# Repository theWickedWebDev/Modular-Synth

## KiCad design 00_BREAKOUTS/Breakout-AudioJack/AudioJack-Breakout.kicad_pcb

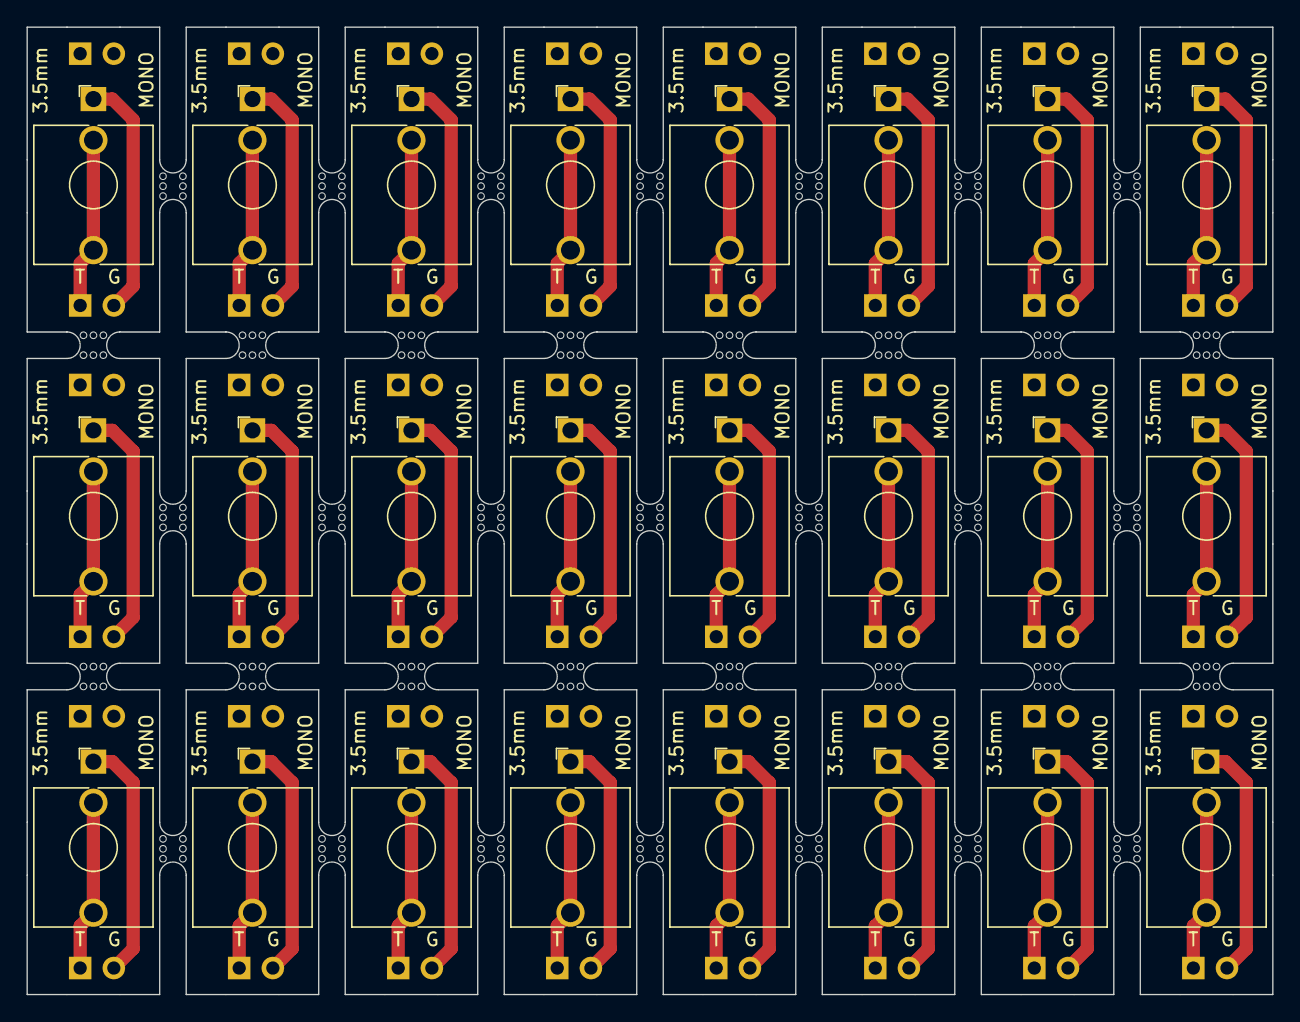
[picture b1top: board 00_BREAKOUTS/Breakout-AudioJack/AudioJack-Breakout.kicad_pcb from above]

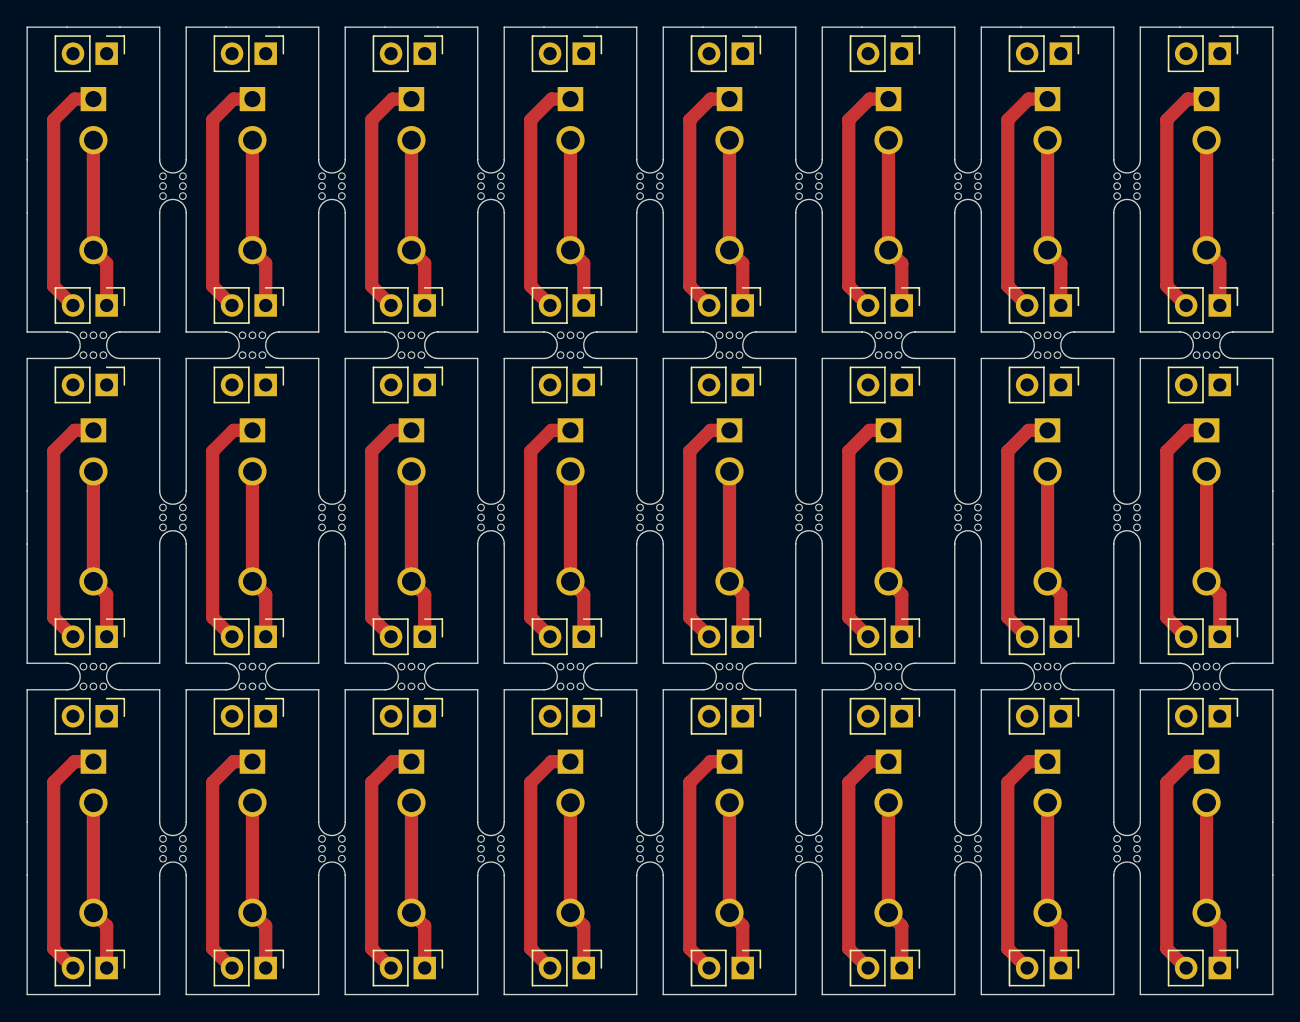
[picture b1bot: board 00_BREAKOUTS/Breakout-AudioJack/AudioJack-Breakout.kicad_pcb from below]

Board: 2 copper layers, 94.0 x 73.0 mm, 109 parts (48 on the bottom side), 2 nets.

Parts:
J3, J5, J7, J12, J15, J18, J21, J24, J27, J30, J33, J36, J39, J42, J45, J48, J51, J54, J57, J60, J63, J66, J69, J72: AudioJack2_Ground; 3.5mm-mono-jack-eurorack-2
J4, J6, J8, J9, J10, J11, J13, J14, J16, J17, J19, J20, J22, J23, J25, J26, J28, J29, J31, J32, J34, J35, J37, J38, J40, J41, J43, J44, J46, J47, J49, J50, J52, J53, J55, J56, J58, J59, J61, J62, J64, J65, J67, J68, J70, J71, J73, J74: Conn_01x02; PinHeader_1x02_P2.54mm_Vertical
mouse-bite-2mm-slot1, mouse-bite-2mm-slot1#2, mouse-bite-2mm-slot2, mouse-bite-2mm-slot3, mouse-bite-2mm-slot4, mouse-bite-2mm-slot5, mouse-bite-2mm-slot6, mouse-bite-2mm-slot7, mouse-bite-2mm-slot8, mouse-bite-2mm-slot9, mouse-bite-2mm-slot10, mouse-bite-2mm-slot11, mouse-bite-2mm-slot12, mouse-bite-2mm-slot13, mouse-bite-2mm-slot14, mouse-bite-2mm-slot16, mouse-bite-2mm-slot17, mouse-bite-2mm-slot18, mouse-bite-2mm-slot19, mouse-bite-2mm-slot20, mouse-bite-2mm-slot21, mouse-bite-2mm-slot22, mouse-bite-2mm-slot23, mouse-bite-2mm-slot24, mouse-bite-2mm-slot25, mouse-bite-2mm-slot26, mouse-bite-2mm-slot27, mouse-bite-2mm-slot28, mouse-bite-2mm-slot29, mouse-bite-2mm-slot30, mouse-bite-2mm-slot33, mouse-bite-2mm-slot35, mouse-bite-2mm-slot37, mouse-bite-2mm-slot39, mouse-bite-2mm-slot41, mouse-bite-2mm-slot43, mouse-bite-2mm-slot45: VAL**; mouse-bite-2mm-slot

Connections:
unnamed: J3.G, J4.2, J5.G, J6.2, J7.G, J10.2, J12.G, J13.2, J15.G, J16.2, J18.G, J19.2, J21.G, J22.2, J24.G, J25.2, J27.G, J28.2, J30.G, J31.2, J33.G, J34.2, J36.G, J37.2, J39.G, J40.2, J42.G, J43.2, J45.G, J46.2, J48.G, J49.2, J51.G, J52.2, J54.G, J55.2, J57.G, J58.2, J60.G, J61.2, J63.G, J64.2, J66.G, J67.2, J69.G, J70.2, J72.G, J73.2
unnamed: J3.S, J3.T, J4.1, J5.S, J5.T, J6.1, J7.S, J7.T, J10.1, J12.S, J12.T, J13.1, J15.S, J15.T, J16.1, J18.S, J18.T, J19.1, J21.S, J21.T, J22.1, J24.S, J24.T, J25.1, J27.S, J27.T, J28.1, J30.S, J30.T, J31.1, J33.S, J33.T, J34.1, J36.S, J36.T, J37.1, J39.S, J39.T, J40.1, J42.S, J42.T, J43.1, J45.S, J45.T, J46.1, J48.S, J48.T, J49.1, J51.S, J51.T, J52.1, J54.S, J54.T, J55.1, J57.S, J57.T, J58.1, J60.S, J60.T, J61.1, J63.S, J63.T, J64.1, J66.S, J66.T, J67.1, J69.S, J69.T, J70.1, J72.S, J72.T, J73.1

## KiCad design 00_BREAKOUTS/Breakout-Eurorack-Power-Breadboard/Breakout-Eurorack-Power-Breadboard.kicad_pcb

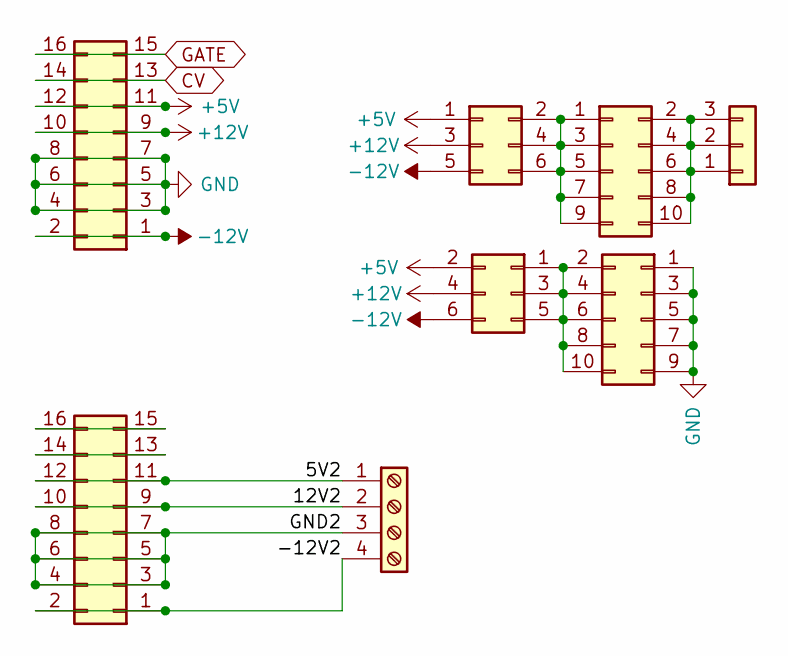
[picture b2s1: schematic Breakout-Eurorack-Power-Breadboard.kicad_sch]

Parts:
J1, J7: Conn_02x20_Odd_Even; IDC-Header_2x08_P2.54mm_Vertical
J2, J3: Conn_02x02_Odd_Even; PinHeader_2x05_P2.54mm_Vertical
J4, J5: Conn_02x03_Odd_Even; PinHeader_2x03_P2.54mm_Vertical
J6: Conn_01x03; PinHeader_1x03_P2.54mm_Vertical
J8: Screw_Terminal_01x04; TerminalBlock_Phoenix_MKDS-1,5-4_1x04_P5.00mm_Horizontal

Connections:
+5V: J1.11, J1.12, J4.2, J5.1
+12V: J1.9, J1.10, J4.4, J5.3
-12V: J1.1, J1.2, J4.6, J5.5
/5V2: J7.11, J7.12, J8.1
/12V2: J7.9, J7.10, J8.2
/-12V2: J7.1, J7.2, J8.4
/GND2: J7.3, J7.4, J7.5, J7.6, J7.7, J7.8, J8.3
CV: J1.13, J1.14
GATE: J1.15, J1.16
GND: J1.3, J1.4, J1.5, J1.6, J1.7, J1.8, J3.1, J3.3, J3.5, J3.7, J3.9
unnamed: J2.1, J2.3, J2.5, J2.7, J2.9, J5.2, J5.4, J5.6
unnamed: J2.2, J2.4, J2.6, J2.8, J2.10, J6.1, J6.2, J6.3
unnamed: J3.2, J3.4, J3.6, J3.8, J3.10, J4.1, J4.3, J4.5
unnamed: J7.13, J7.14
unnamed: J7.15, J7.16

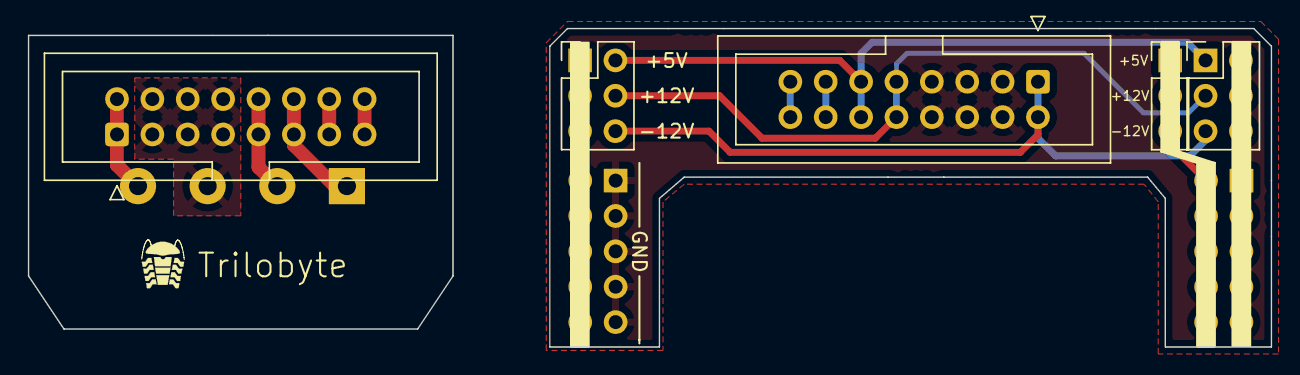
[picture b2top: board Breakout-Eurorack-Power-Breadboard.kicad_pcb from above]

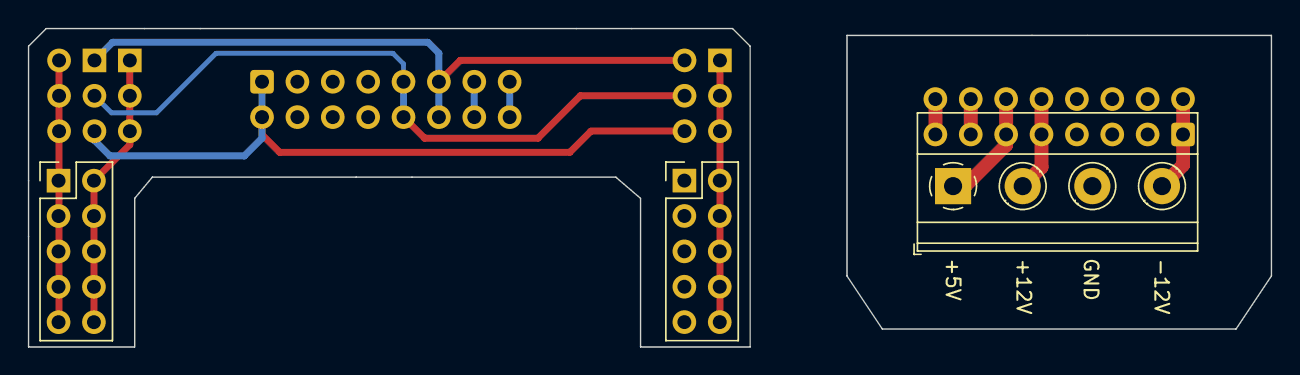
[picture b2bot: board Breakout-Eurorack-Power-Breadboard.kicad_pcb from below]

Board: 2 copper layers, 89.2 x 22.9 mm, 8 parts (3 on the bottom side), 15 nets.

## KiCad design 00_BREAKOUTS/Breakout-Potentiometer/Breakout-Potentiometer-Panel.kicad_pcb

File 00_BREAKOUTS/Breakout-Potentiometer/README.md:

# Potentiometer - Breakout Boards

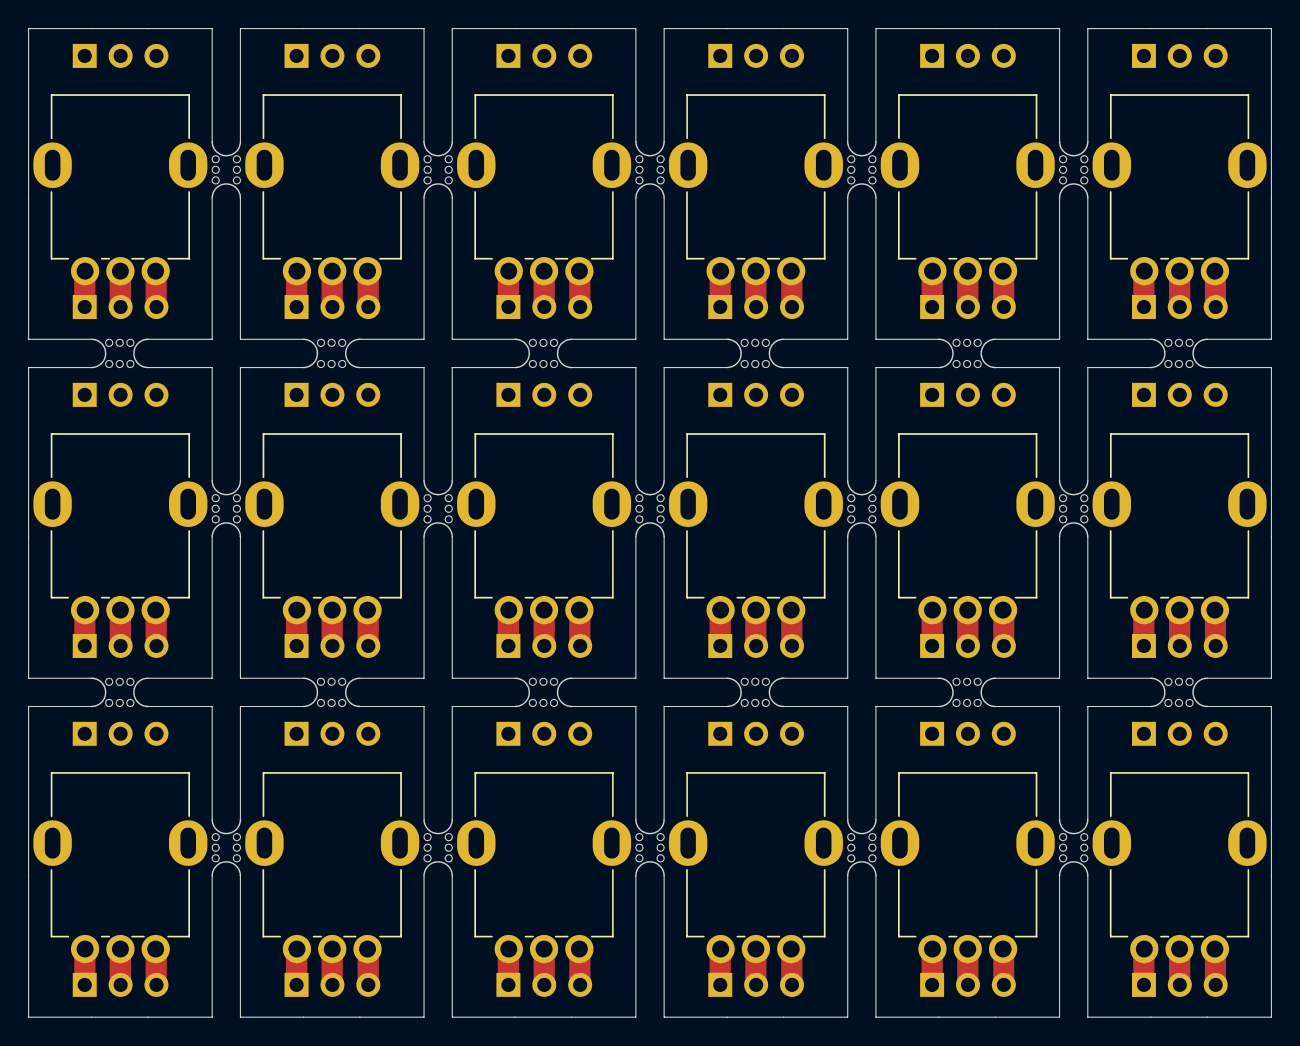
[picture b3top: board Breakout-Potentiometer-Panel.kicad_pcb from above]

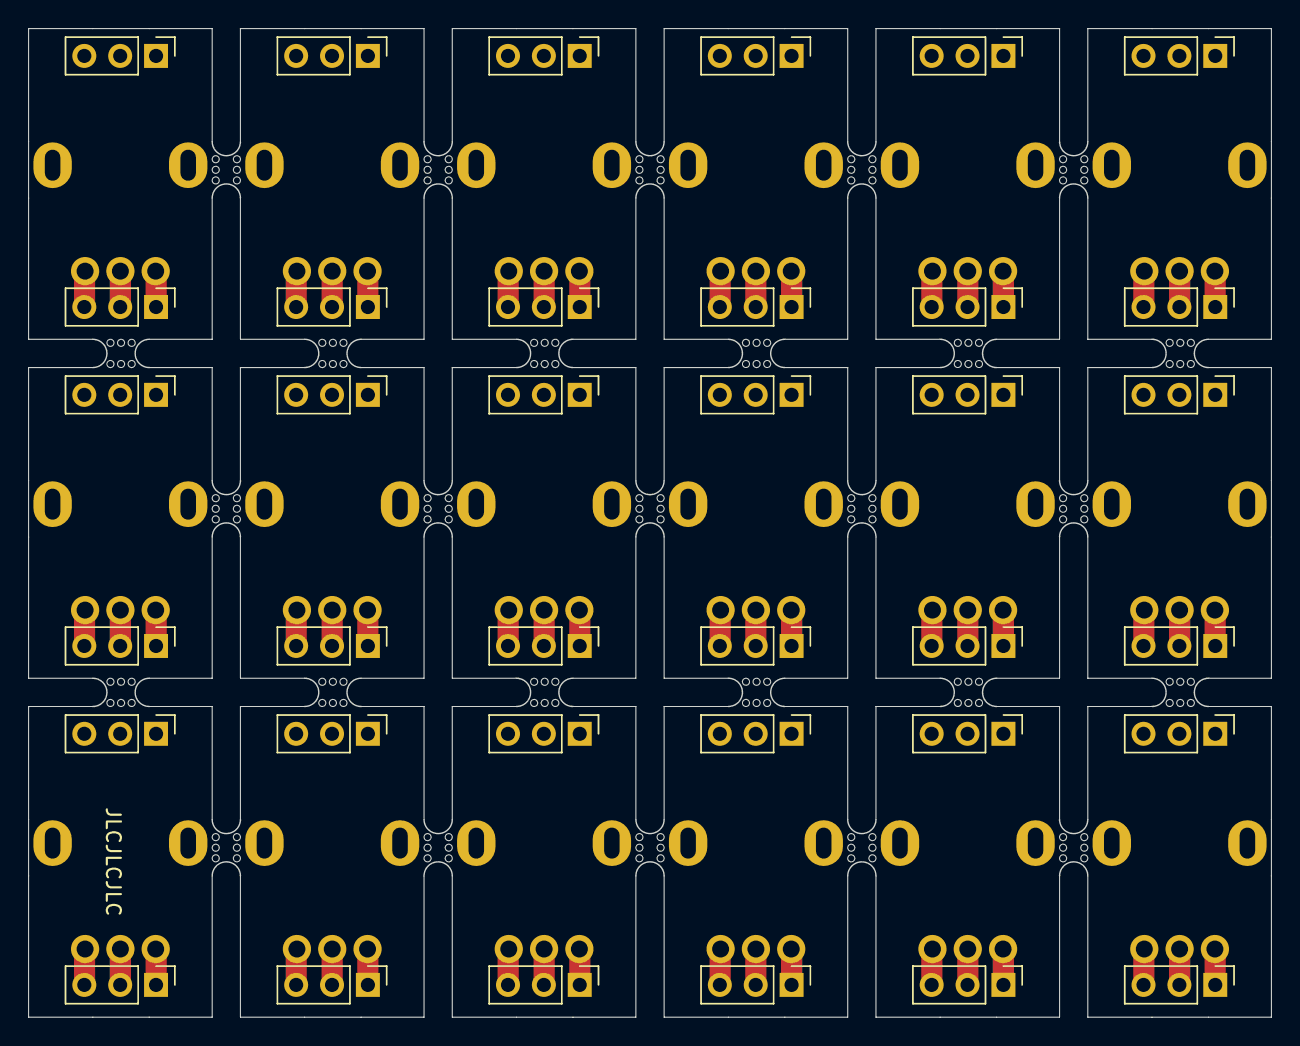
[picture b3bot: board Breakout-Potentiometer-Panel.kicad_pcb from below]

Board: 2 copper layers, 88.0 x 70.0 mm, 81 parts (36 on the bottom side), 3 nets.

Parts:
J1, J2, J3, J4, J5, J6, J7, J8, J9, J10, J11, J12, J13, J14, J15, J16, J17, J18, J19, J20, J21, J22, J23, J24, J25, J26, J27, J28, J29, J30, J31, J32, J33, J34, J35, J36: Conn_01x03; PinHeader_1x03_P2.54mm_Vertical
RV1, RV2, RV3, RV4, RV5, RV6, RV7, RV8, RV9, RV10, RV11, RV12, RV13, RV14, RV15, RV16, RV17, RV18: R_Potentiometer_US; alpha-9mm-potentiometer
mouse-bite-2mm-slot1, mouse-bite-2mm-slot3, mouse-bite-2mm-slot5, mouse-bite-2mm-slot7, mouse-bite-2mm-slot9, mouse-bite-2mm-slot12, mouse-bite-2mm-slot13, mouse-bite-2mm-slot14, mouse-bite-2mm-slot15, mouse-bite-2mm-slot16, mouse-bite-2mm-slot17, mouse-bite-2mm-slot18, mouse-bite-2mm-slot19, mouse-bite-2mm-slot20, mouse-bite-2mm-slot21, mouse-bite-2mm-slot22, mouse-bite-2mm-slot24, mouse-bite-2mm-slot25, mouse-bite-2mm-slot26, mouse-bite-2mm-slot27, mouse-bite-2mm-slot28, mouse-bite-2mm-slot29, mouse-bite-2mm-slot30, mouse-bite-2mm-slot31, mouse-bite-2mm-slot32, mouse-bite-2mm-slot33, mouse-bite-2mm-slot34: VAL**; mouse-bite-2mm-slot

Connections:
unnamed: J2.1, J4.1, J6.1, J8.1, J10.1, J12.1, J14.1, J16.1, J18.1, J20.1, J22.1, J24.1, J26.1, J28.1, J30.1, J32.1, J34.1, J36.1, RV1.1, RV2.1, RV3.1, RV4.1, RV5.1, RV6.1, RV7.1, RV8.1, RV9.1, RV10.1, RV11.1, RV12.1, RV13.1, RV14.1, RV15.1, RV16.1, RV17.1, RV18.1
unnamed: J2.2, J4.2, J6.2, J8.2, J10.2, J12.2, J14.2, J16.2, J18.2, J20.2, J22.2, J24.2, J26.2, J28.2, J30.2, J32.2, J34.2, J36.2, RV1.2, RV2.2, RV3.2, RV4.2, RV5.2, RV6.2, RV7.2, RV8.2, RV9.2, RV10.2, RV11.2, RV12.2, RV13.2, RV14.2, RV15.2, RV16.2, RV17.2, RV18.2
unnamed: J2.3, J4.3, J6.3, J8.3, J10.3, J12.3, J14.3, J16.3, J18.3, J20.3, J22.3, J24.3, J26.3, J28.3, J30.3, J32.3, J34.3, J36.3, RV1.3, RV2.3, RV3.3, RV4.3, RV5.3, RV6.3, RV7.3, RV8.3, RV9.3, RV10.3, RV11.3, RV12.3, RV13.3, RV14.3, RV15.3, RV16.3, RV17.3, RV18.3

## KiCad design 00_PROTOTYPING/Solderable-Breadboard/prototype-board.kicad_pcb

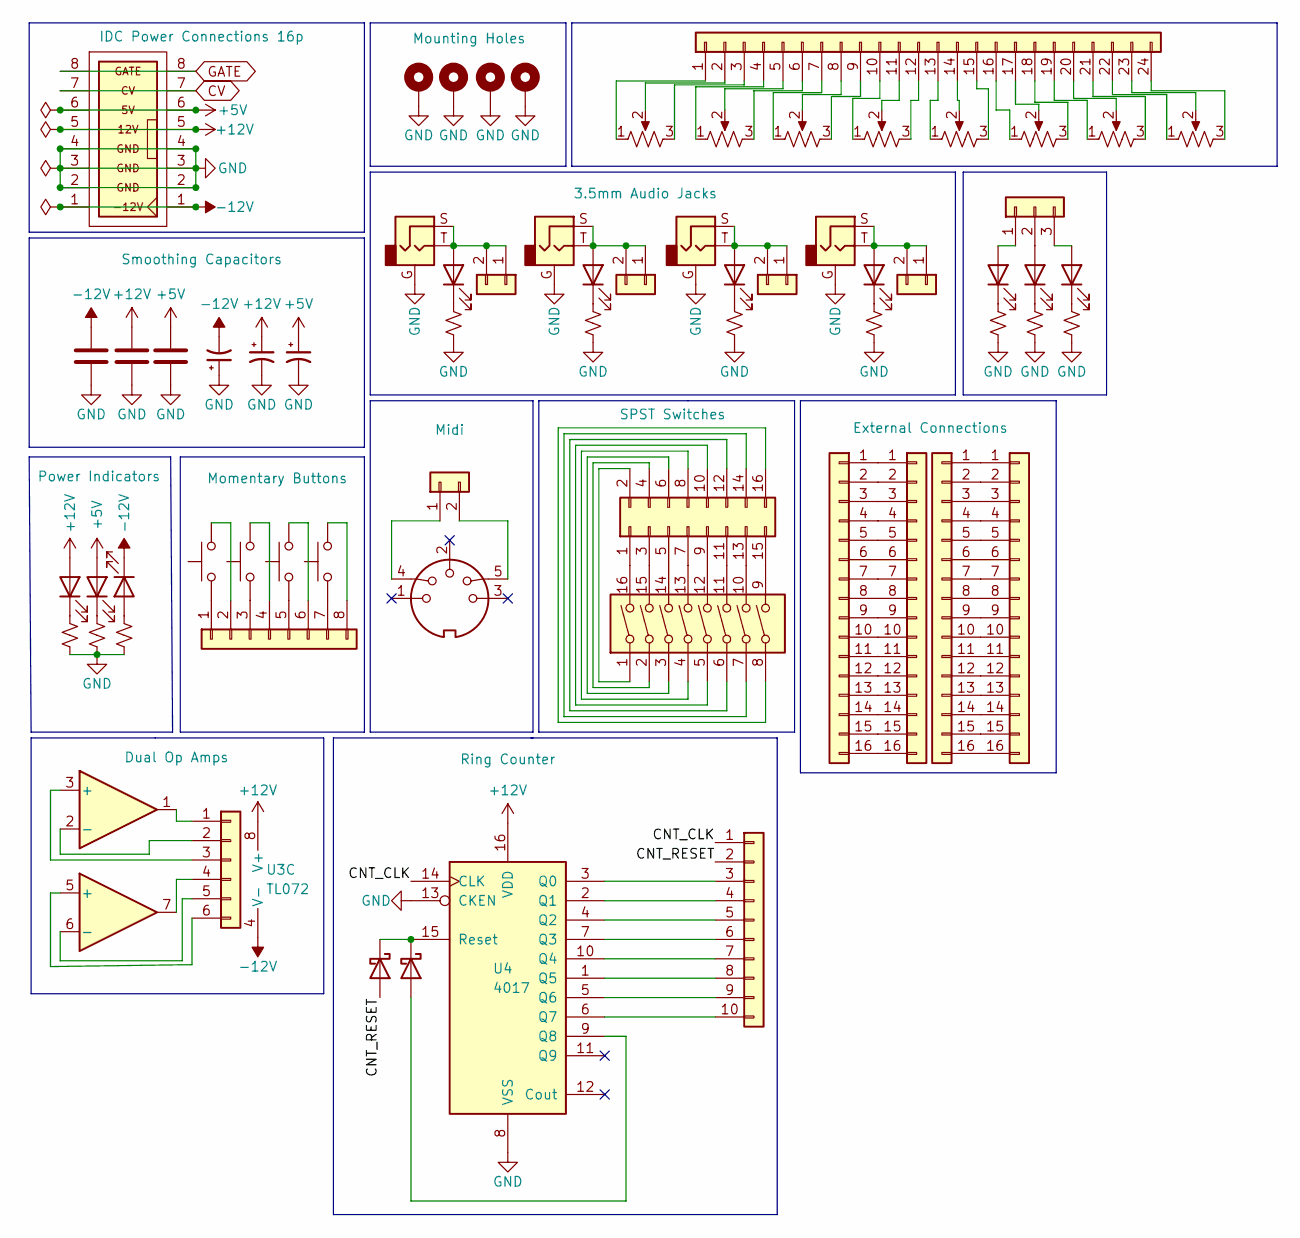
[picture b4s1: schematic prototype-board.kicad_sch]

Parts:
C1, C2, C3: C; C_0805_2012Metric
C4, C5, C6: C_Polarized_Small_US; CP_Elec_6.3x7.7
D1, D2, D3, D4, D5, D6, D7, D8, D11, D12: LED; LED_0805_2012Metric-Blue
D9, D10: BAT43W-V; D_SOD-123
H1, H2, H3, H4: MountingHole_Pad; MountingHole_3mm_Pad_Via
J1, J4, J6, J8, J20: Conn_01x02; PinHeader_1x02_P2.54mm_Vertical
J2, J3, J5, J7: AudioJack2_Ground; 3.5mm-mono-jack-eurorack-2
J9: Conn_01x24; PinSocket_1x24_P2.54mm_Vertical
J10: Conn_01x03; PinHeader_1x03_P2.54mm_Vertical
J11: Conn_02x08_Odd_Even; PinHeader_2x08_P2.54mm_Vertical
J12: Conn_01x06; PinHeader_1x06_P2.54mm_Vertical
J13: Conn_01x10; PinHeader_1x10_P2.54mm_Vertical
J15, J17: Conn_01x16; PinHeader_1x16_P2.54mm_Vertical
J16, J18: Conn_01x16; PinHeader_1x16_P2.54mm_Horizontal
J19: DIN-5_180degree; MIDI_DIN5
J21: Conn_01x08; PinHeader_1x08_P2.54mm_Vertical
R1, R2, R3, R4, R5, R6, R7, R8, R9, R10: R_Small_US; R_0805_2012Metric
RV1, RV2, RV3, RV4, RV5, RV6, RV7, RV8: R_Potentiometer_US; alpha-9mm-potentiometer
SW1: SW_DIP_x08; SW_DIP_SPSTx08_Slide_9.78x22.5mm_W7.62mm_P2.54mm
SW2, SW3, SW4, SW5: SW_Push; SW_PUSH_6mm
U1: Eurorack_IDE_16P; IDC-Socket-Eurorack_16p_2.54mm
U3: TL072; DIP-8_W7.62mm
U4: 4017; SOIC-16_3.9x9.9mm_P1.27mm

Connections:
+5V: C3.1, C6.1, D7.2 (A), U1.6 (5V)
+12V: C2.1, C4.1, D6.2 (A), U1.5 (12V), U3.8 (V+), U4.16 (VDD)
-12V: C1.1, C5.2, D8.1 (K), U1.1 (-12V), U3.4 (V-)
/CNT_CLK: J13.1, U4.14 (CLK)
/CNT_RESET: D9.2 (A), J13.2
CV: U1.7 (CV)
GATE: U1.8 (GATE)
GND: C1.2, C2.2, C3.2, C4.2, C5.1, C6.2, H1.1, H2.1, H3.1, H4.1, J2.G, J3.G, J5.G, J7.G, R1.2, R2.2, R3.2, R4.2, R5.2, R6.2, R7.2, R8.2, R9.2, R10.2, U1.2 (GND), U1.3 (GND), U1.4 (GND), U4.8 (VSS), U4.13 (CKEN)
unnamed: D1.1 (K), R1.1
unnamed: D1.2 (A), J1.1, J1.2, J3.S, J3.T
unnamed: D2.1 (K), R2.1
unnamed: D2.2 (A), J2.S, J2.T, J4.1, J4.2
unnamed: D3.1 (K), R3.1
unnamed: D3.2 (A), J5.S, J5.T, J6.1, J6.2
unnamed: D4.1 (K), R4.1
unnamed: D4.2 (A), J7.S, J7.T, J8.1, J8.2
unnamed: D5.1 (K), R5.1
unnamed: D5.2 (A), J10.1
unnamed: D6.1 (K), R8.1
unnamed: D7.1 (K), R9.1
unnamed: D8.2 (A), R10.1
unnamed: D9.1 (K), D10.1 (K), U4.15 (Reset)
unnamed: D10.2 (A), U4.9 (Q8)
unnamed: D11.1 (K), R6.1
unnamed: D11.2 (A), J10.2
unnamed: D12.1 (K), R7.1
unnamed: D12.2 (A), J10.3
unnamed: J9.1, RV1.1
unnamed: J9.2, RV1.2
unnamed: J9.3, RV1.3
unnamed: J9.4, RV2.1
unnamed: J9.5, RV2.2
unnamed: J9.6, RV2.3
unnamed: J9.7, RV3.1
unnamed: J9.8, RV3.2
unnamed: J9.9, RV3.3
unnamed: J9.10, RV4.1
unnamed: J9.11, RV4.2
unnamed: J9.12, RV4.3
unnamed: J9.13, RV5.1
unnamed: J9.14, RV5.2
unnamed: J9.15, RV5.3
unnamed: J9.16, RV6.1
unnamed: J9.17, RV6.2
unnamed: J9.18, RV6.3
unnamed: J9.19, RV7.1
unnamed: J9.20, RV7.2
unnamed: J9.21, RV7.3
unnamed: J9.22, RV8.1
unnamed: J9.23, RV8.2
unnamed: J9.24, RV8.3
unnamed: J11.1, SW1.16
unnamed: J11.2, SW1.1
unnamed: J11.3, SW1.15
unnamed: J11.4, SW1.2
unnamed: J11.5, SW1.14
unnamed: J11.6, SW1.3
unnamed: J11.7, SW1.13
unnamed: J11.8, SW1.4
unnamed: J11.9, SW1.12
unnamed: J11.10, SW1.5
unnamed: J11.11, SW1.11
unnamed: J11.12, SW1.6
unnamed: J11.13, SW1.10
unnamed: J11.14, SW1.7
unnamed: J11.15, SW1.9
unnamed: J11.16, SW1.8
unnamed: J12.1, U3.1
unnamed: J12.2, U3.2 (-)
unnamed: J12.3, U3.3 (+)
unnamed: J12.4, U3.7
unnamed: J12.5, U3.6 (-)
unnamed: J12.6, U3.5 (+)
unnamed: J13.3, U4.3 (Q0)
unnamed: J13.4, U4.2 (Q1)
unnamed: J13.5, U4.4 (Q2)
unnamed: J13.6, U4.7 (Q3)
unnamed: J13.7, U4.10 (Q4)
unnamed: J13.8, U4.1 (Q5)
unnamed: J13.9, U4.5 (Q6)
unnamed: J13.10, U4.6 (Q7)
unnamed: J15.1, J16.1
unnamed: J15.2, J16.2
unnamed: J15.3, J16.3
unnamed: J15.4, J16.4
unnamed: J15.5, J16.5
unnamed: J15.6, J16.6
unnamed: J15.7, J16.7
unnamed: J15.8, J16.8
unnamed: J15.9, J16.9
unnamed: J15.10, J16.10
unnamed: J15.11, J16.11
unnamed: J15.12, J16.12
unnamed: J15.13, J16.13
unnamed: J15.14, J16.14
unnamed: J15.15, J16.15
unnamed: J15.16, J16.16
unnamed: J17.1, J18.1
unnamed: J17.2, J18.2
unnamed: J17.3, J18.3
unnamed: J17.4, J18.4
unnamed: J17.5, J18.5
unnamed: J17.6, J18.6
unnamed: J17.7, J18.7
unnamed: J17.8, J18.8
unnamed: J17.9, J18.9
unnamed: J17.10, J18.10
unnamed: J17.11, J18.11
unnamed: J17.12, J18.12
unnamed: J17.13, J18.13
unnamed: J17.14, J18.14
unnamed: J17.15, J18.15
unnamed: J17.16, J18.16
unnamed: J19.4, J20.1
unnamed: J19.5, J20.2
unnamed: J21.1, SW2.1
unnamed: J21.2, SW2.2
unnamed: J21.3, SW3.1
unnamed: J21.4, SW3.2
unnamed: J21.5, SW4.1
unnamed: J21.6, SW4.2
unnamed: J21.7, SW5.1
unnamed: J21.8, SW5.2

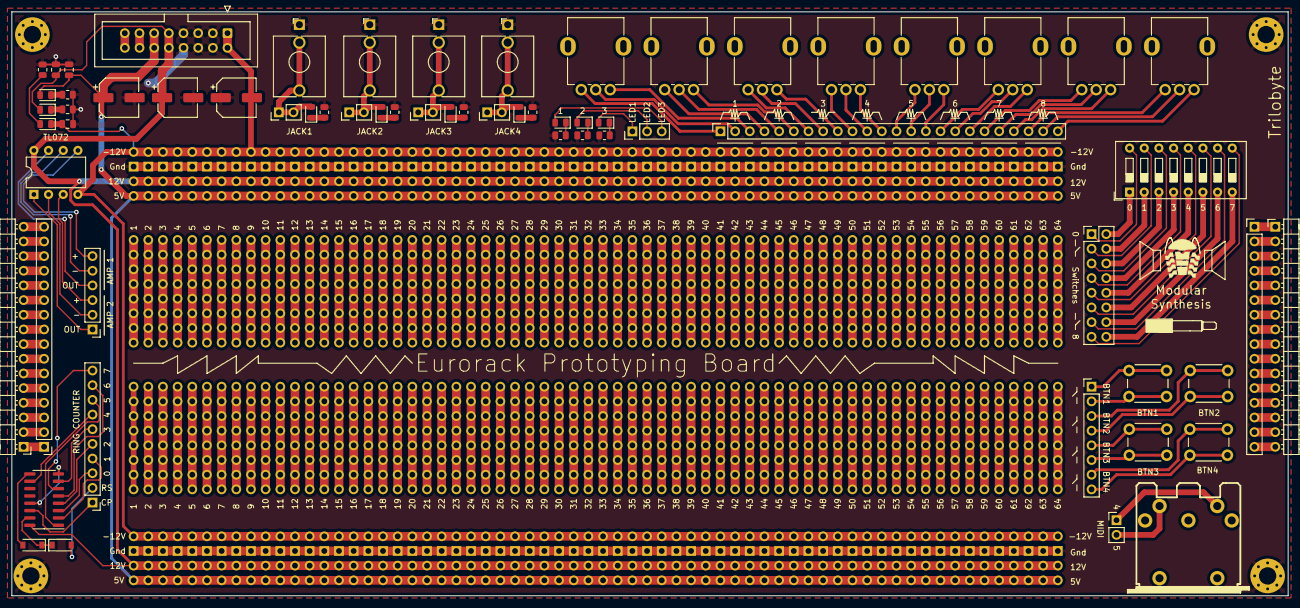
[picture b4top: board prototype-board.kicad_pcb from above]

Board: 2 copper layers, 221.0 x 101.1 mm, 68 parts (0 on the bottom side), 121 nets.

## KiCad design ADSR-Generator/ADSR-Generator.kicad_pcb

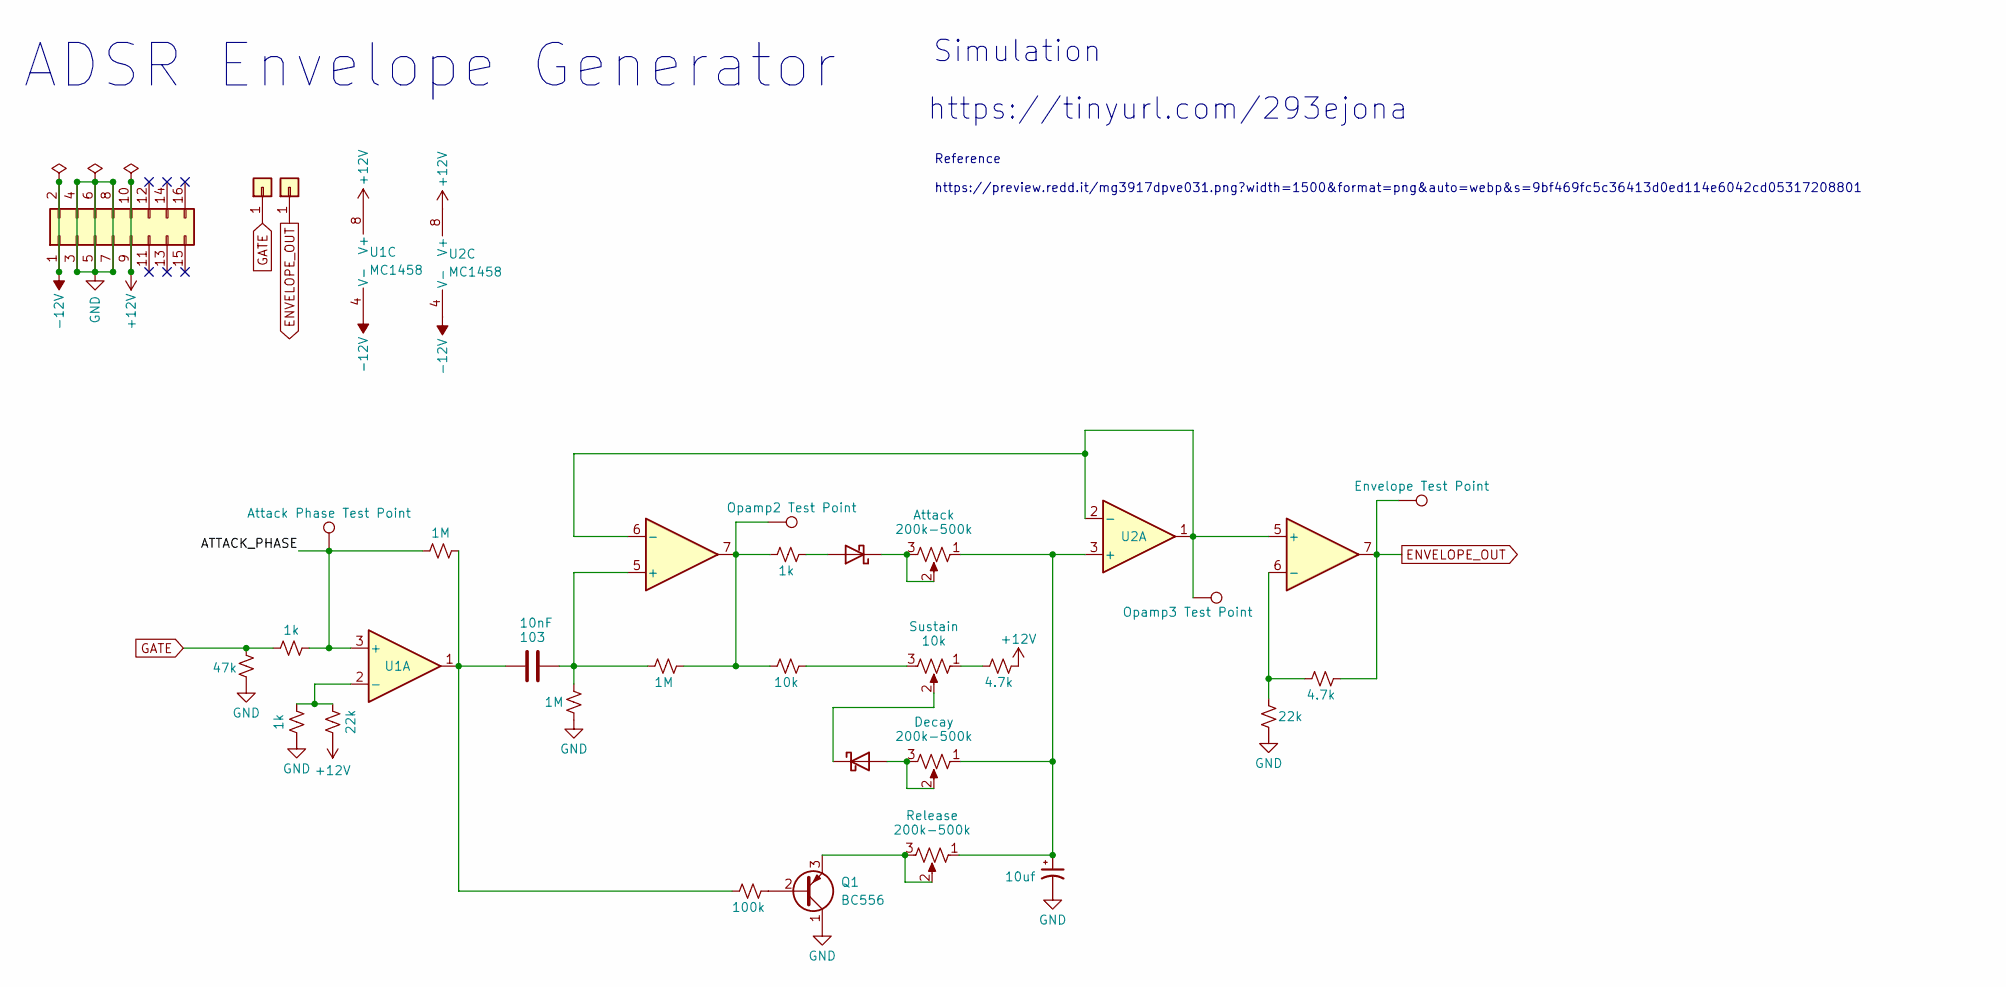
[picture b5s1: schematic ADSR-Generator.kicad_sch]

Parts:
C1: C; C_0805_2012Metric
C2: C_Polarized_Small_US; CP_Elec_5x5.4
D2, D3: BAT43W-V; D_SOD-123
J1: Conn_02x20_Odd_Even; IDC-Header_2x08_P2.54mm_Vertical
J2, J3: Conn_01x01; ACJS-MV35-3S-audio-jack
Q1: BC556; SOT23-BEC_PNP
R1, R2, R3, R4, R5, R6, R7, R8, R9, R10, R11, R12, R13: R_Small_US; R_0805_2012Metric
RV1, RV2, RV3, RV4: R_Potentiometer_US; Potentiometer_Omeg_PC16BU_Vertical
TP1, TP2, TP3, TP4: TestPoint; TestPoint_Keystone_5019_Minature
U1, U2: MC1458; SOIC-8_3.9x4.9mm_P1.27mm

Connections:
+12V: J1.9, J1.10, R4.2, R11.1, U1.8 (V+), U2.8 (V+)
-12V: J1.1, J1.2, U1.4 (V-), U2.4 (V-)
/ATTACK_PHASE: R2.2, R5.1, TP1.1, U1.3 (+)
ENVELOPE_OUT: J3.1, R13.1, TP4.1, U2.7
GATE: J2.1, R1.1, R2.1
GND: C2.2, J1.3, J1.4, J1.5, J1.6, J1.7, J1.8, Q1.1 (C), R1.2, R3.1, R6.1, R12.2
unnamed: C1.1, R5.2, R8.2, U1.1
unnamed: C1.2, R6.2, R7.2, U1.5 (+)
unnamed: C2.1, RV1.1, RV2.1, RV4.1, U2.3 (+)
unnamed: Q1.2 (B), R8.1
unnamed: Q1.3 (E), RV1.2, RV1.3
unnamed: R3.2, R4.1, U1.2 (-)
unnamed: D2.2 (A), R9.1
unnamed: R10.1, RV3.3
unnamed: R7.1, R9.2, R10.2, TP2.1, U1.7
unnamed: R11.2, RV3.1
unnamed: R12.1, R13.2, U2.6 (-)
unnamed: D2.1 (K), RV2.2, RV2.3
unnamed: D3.1 (K), RV3.2
unnamed: D3.2 (A), RV4.2, RV4.3
unnamed: TP3.1, U1.6 (-), U2.1, U2.2 (-), U2.5 (+)

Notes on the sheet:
ADSR Envelope Generator
https://tinyurl.com/293ejona
Reference https://preview.redd.it/mg3917dpve031.png?width=1500&format=png&auto=webp&s=9bf469fc5c36413d0ed114e6042cd05317208801
Simulation

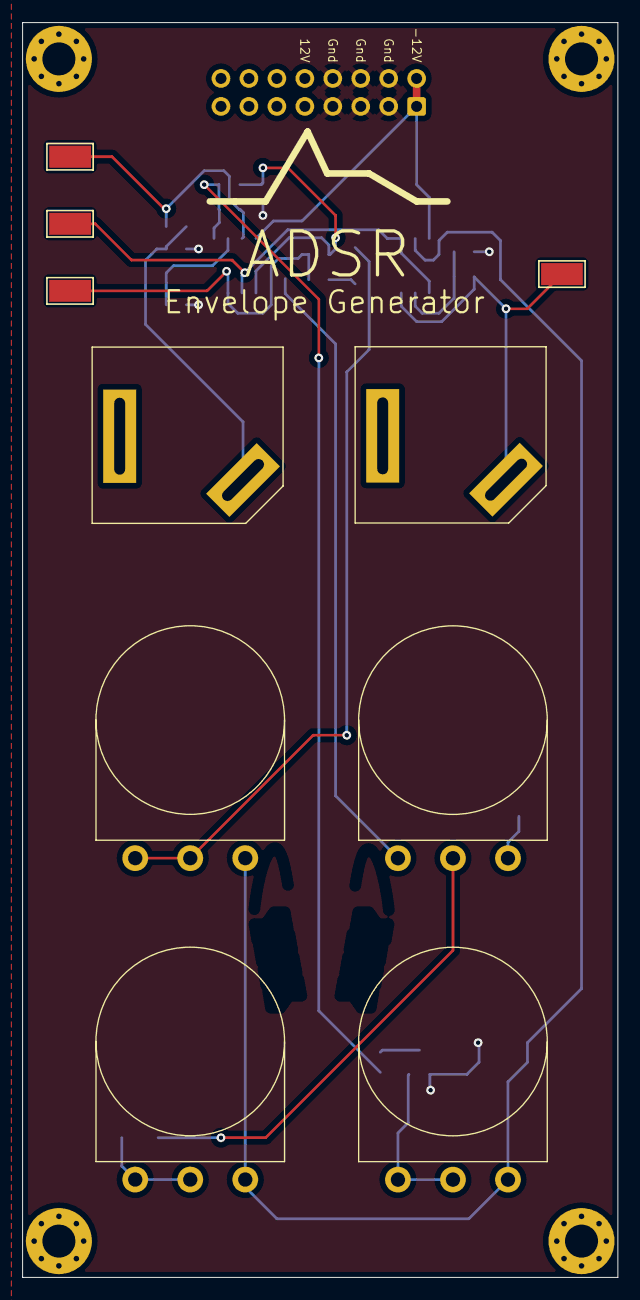
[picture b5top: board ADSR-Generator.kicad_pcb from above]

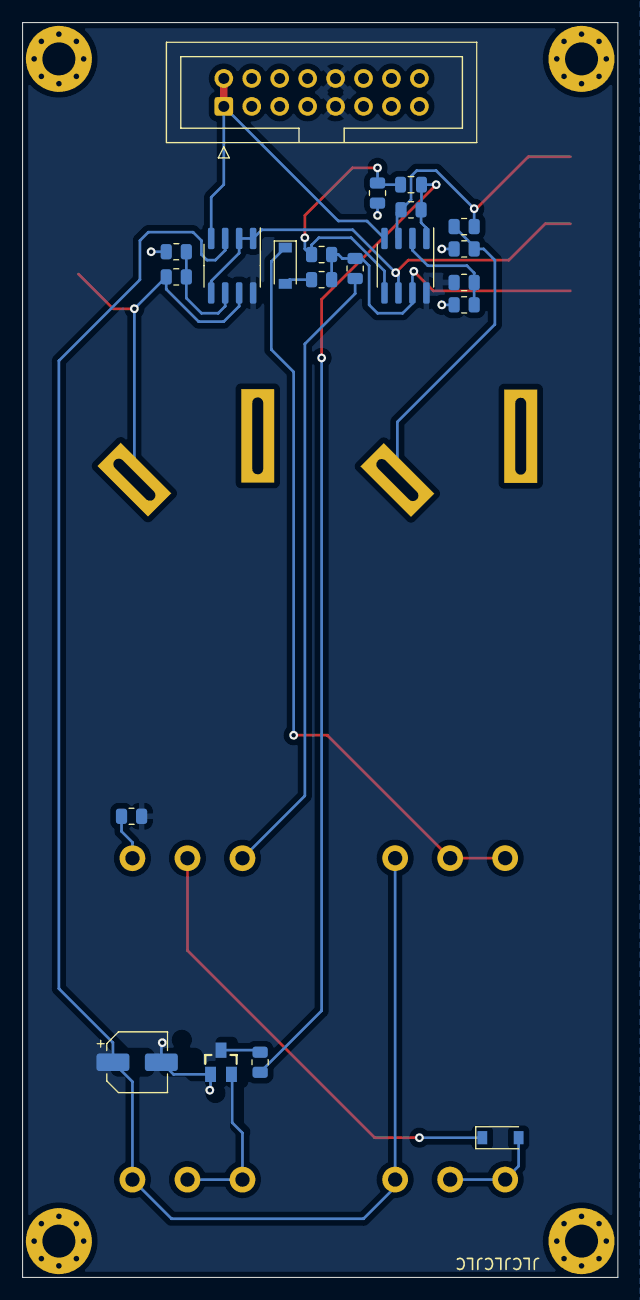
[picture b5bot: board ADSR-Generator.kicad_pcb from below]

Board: 2 copper layers, 54.1 x 114.0 mm, 31 parts (21 on the bottom side), 21 nets.

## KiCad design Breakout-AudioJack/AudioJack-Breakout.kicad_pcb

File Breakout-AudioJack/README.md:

# Audio Jack 3.5mm - Breakout Boards

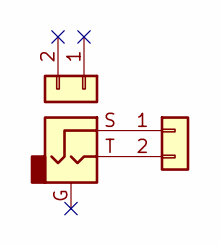
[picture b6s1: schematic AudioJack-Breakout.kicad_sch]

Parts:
J3: AudioJack2_Ground; 3.5mm-mono-jack-eurorack-2
J4, J8: Conn_01x02; PinHeader_1x02_P2.54mm_Vertical

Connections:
unnamed: J3.S, J4.1
unnamed: J3.T, J4.2

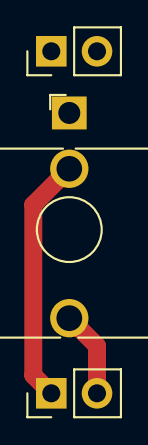
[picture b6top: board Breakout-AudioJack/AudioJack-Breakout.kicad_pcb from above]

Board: 2 copper layers, 3 parts (0 on the bottom side), 2 nets.

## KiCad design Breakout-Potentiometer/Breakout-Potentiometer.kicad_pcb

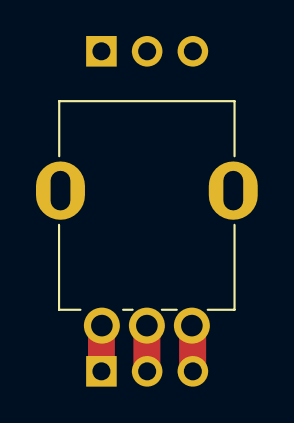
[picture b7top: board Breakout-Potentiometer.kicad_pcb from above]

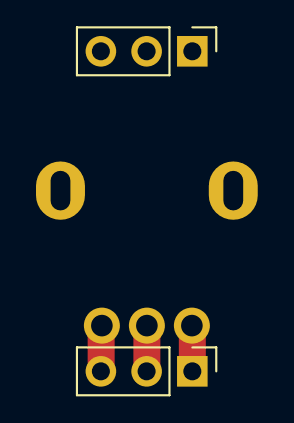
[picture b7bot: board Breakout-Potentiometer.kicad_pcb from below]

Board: 2 copper layers, 3 parts (2 on the bottom side), 3 nets.

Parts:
J1, J2: Conn_01x03; PinHeader_1x03_P2.54mm_Vertical
RV1: R_Potentiometer_US; alpha-9mm-potentiometer

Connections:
unnamed: J2.1, RV1.1
unnamed: J2.2, RV1.2
unnamed: J2.3, RV1.3
